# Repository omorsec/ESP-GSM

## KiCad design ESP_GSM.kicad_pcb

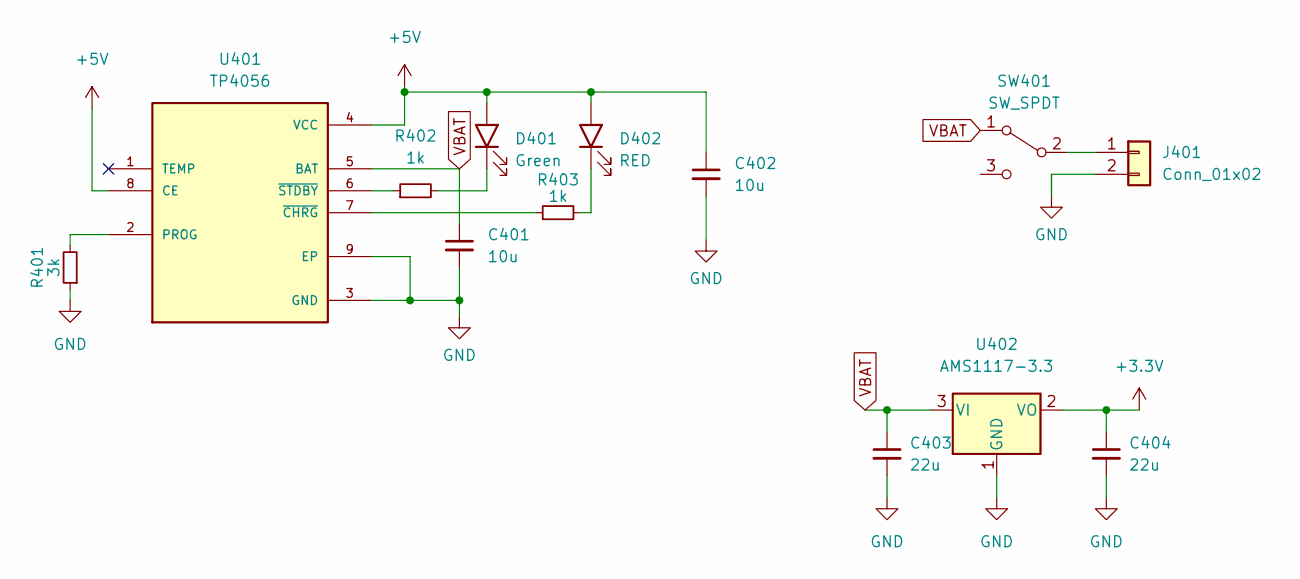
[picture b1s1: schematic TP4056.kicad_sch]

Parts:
C401, C402: 10u; CP_EIA-3216-10_Kemet-I; JLCPCB Part No C7171
C403, C404: 22u; CP_EIA-3216-10_Kemet-I; JLCPCB Part No C782264
D401: Green; LED_0402_1005Metric; JLCPCB Part No C965797
D402: RED; LED_0402_1005Metric; JLCPCB Part No C130719
J401: Conn_01x02; JST_PH_S2B-PH-K_1x02_P2.00mm_Horizontal; JLCPCB Part No C173752
R401: 3k; R_0805_2012Metric; JLCPCB Part No C17661
R402, R403: 1k; R_0402_1005Metric; JLCPCB Part No C2693046
SW401: SW_SPDT; SW_Slide_1P2T_CK_OS102011MS2Q; JLCPCB Part No C393937
U401: TP4056; SOP127P600X175-9N; JLCPCB Part No C16581
U402: AMS1117-3.3; SOT-223-3_TabPin2; JLCPCB Part No C6186

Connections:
+3V3: C404.1, U402.2 (VO); also elsewhere on the board
+5V: C402.1, D401.2 (A), D402.2 (A), U401.4 (VCC), U401.8 (CE); also elsewhere on the board
GND: C401.2, C402.2, C403.2, C404.2, J401.2, R401.1, U401.3 (GND), U401.9 (EP), U402.1 (GND); also elsewhere on the board
unnamed: D401.1 (K), R402.2
unnamed: D402.1 (K), R403.2
unnamed: J401.1, SW401.2 (B)
unnamed: R401.2, U401.2 (PROG)
unnamed: R402.1, U401.6 (~STDBY)
unnamed: R403.1, U401.7 (~CHRG)
VBAT: C401.1, C403.1, SW401.1 (A), U401.5 (BAT), U402.3 (VI); also elsewhere on the board

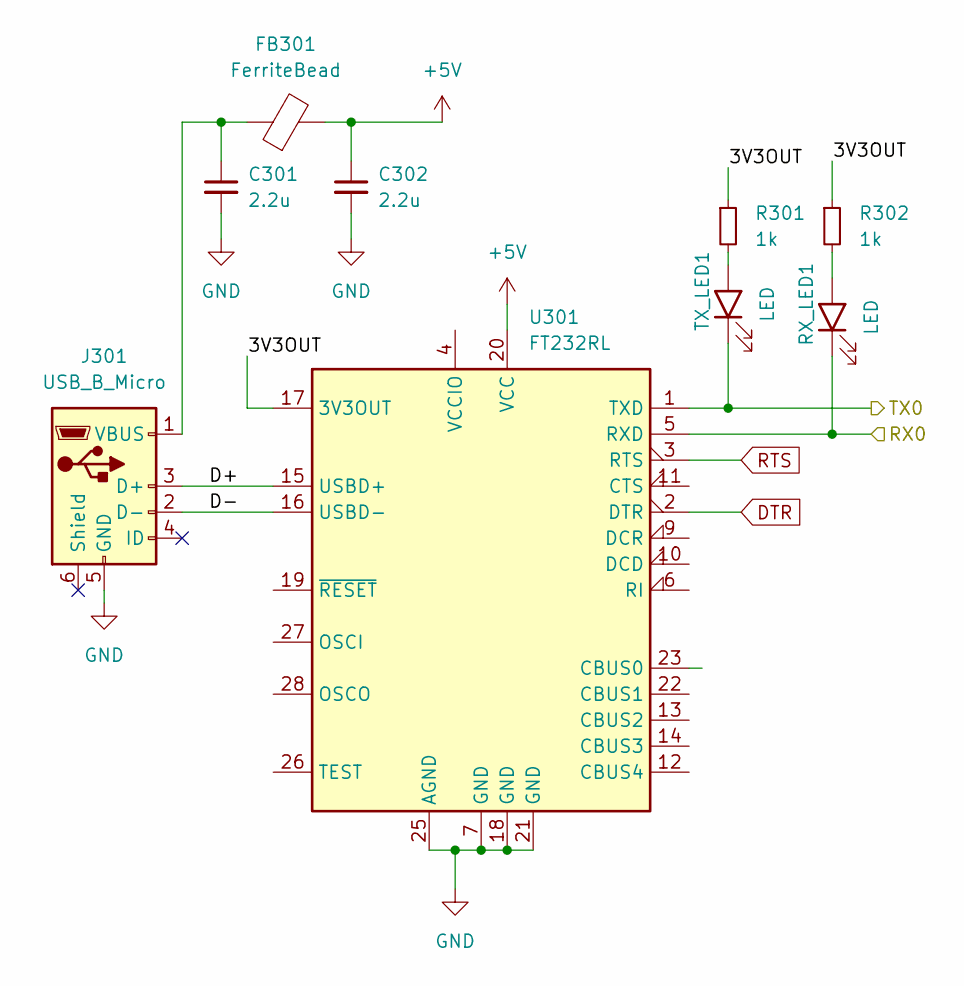
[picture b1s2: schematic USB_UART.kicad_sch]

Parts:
C301, C302: 2.2u; C_0603_1608Metric; JLCPCB Part No C23630
FB301: FerriteBead; L_0805_2012Metric; JLCPCB Part No C1015
J301: USB_B_Micro; USB_Micro-B_Amphenol_10118194_Horizontal; JLCPCB Part No C132563
R301, R302: 1k; R_0402_1005Metric; JLCPCB Part No C2693046
RX_LED1: LED; LED_0402_1005Metric; JLCPCB Part No C130719
TX_LED1: LED; LED_0402_1005Metric; JLCPCB Part No C130719
U301: FT232RL; SSOP-28_5.3x10.2mm_P0.65mm; JLCPCB Part No C8690

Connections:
+5V: C302.1, FB301.2, U301.20 (VCC); also elsewhere on the board
/ESP32/RX0: TX_LED1.1 (K), U301.1 (TXD); also elsewhere on the board
/ESP32/TX0: RX_LED1.1 (K), U301.5 (RXD); also elsewhere on the board
/USB_UART/3V3OUT: R301.1, R302.1, U301.17 (3V3OUT)
/USB_UART/D+: J301.3 (D+), U301.15 (USBD+)
/USB_UART/D-: J301.2 (D-), U301.16 (USBD-)
DTR: U301.2 (DTR); also elsewhere on the board
GND: C301.2, C302.2, J301.5 (GND), U301.7 (GND), U301.18 (GND), U301.21 (GND), U301.25 (AGND); also elsewhere on the board
unnamed: C301.1, FB301.1, J301.1 (VBUS)
unnamed: R301.2, TX_LED1.2 (A)
unnamed: R302.2, RX_LED1.2 (A)
RTS: U301.3 (RTS); also elsewhere on the board

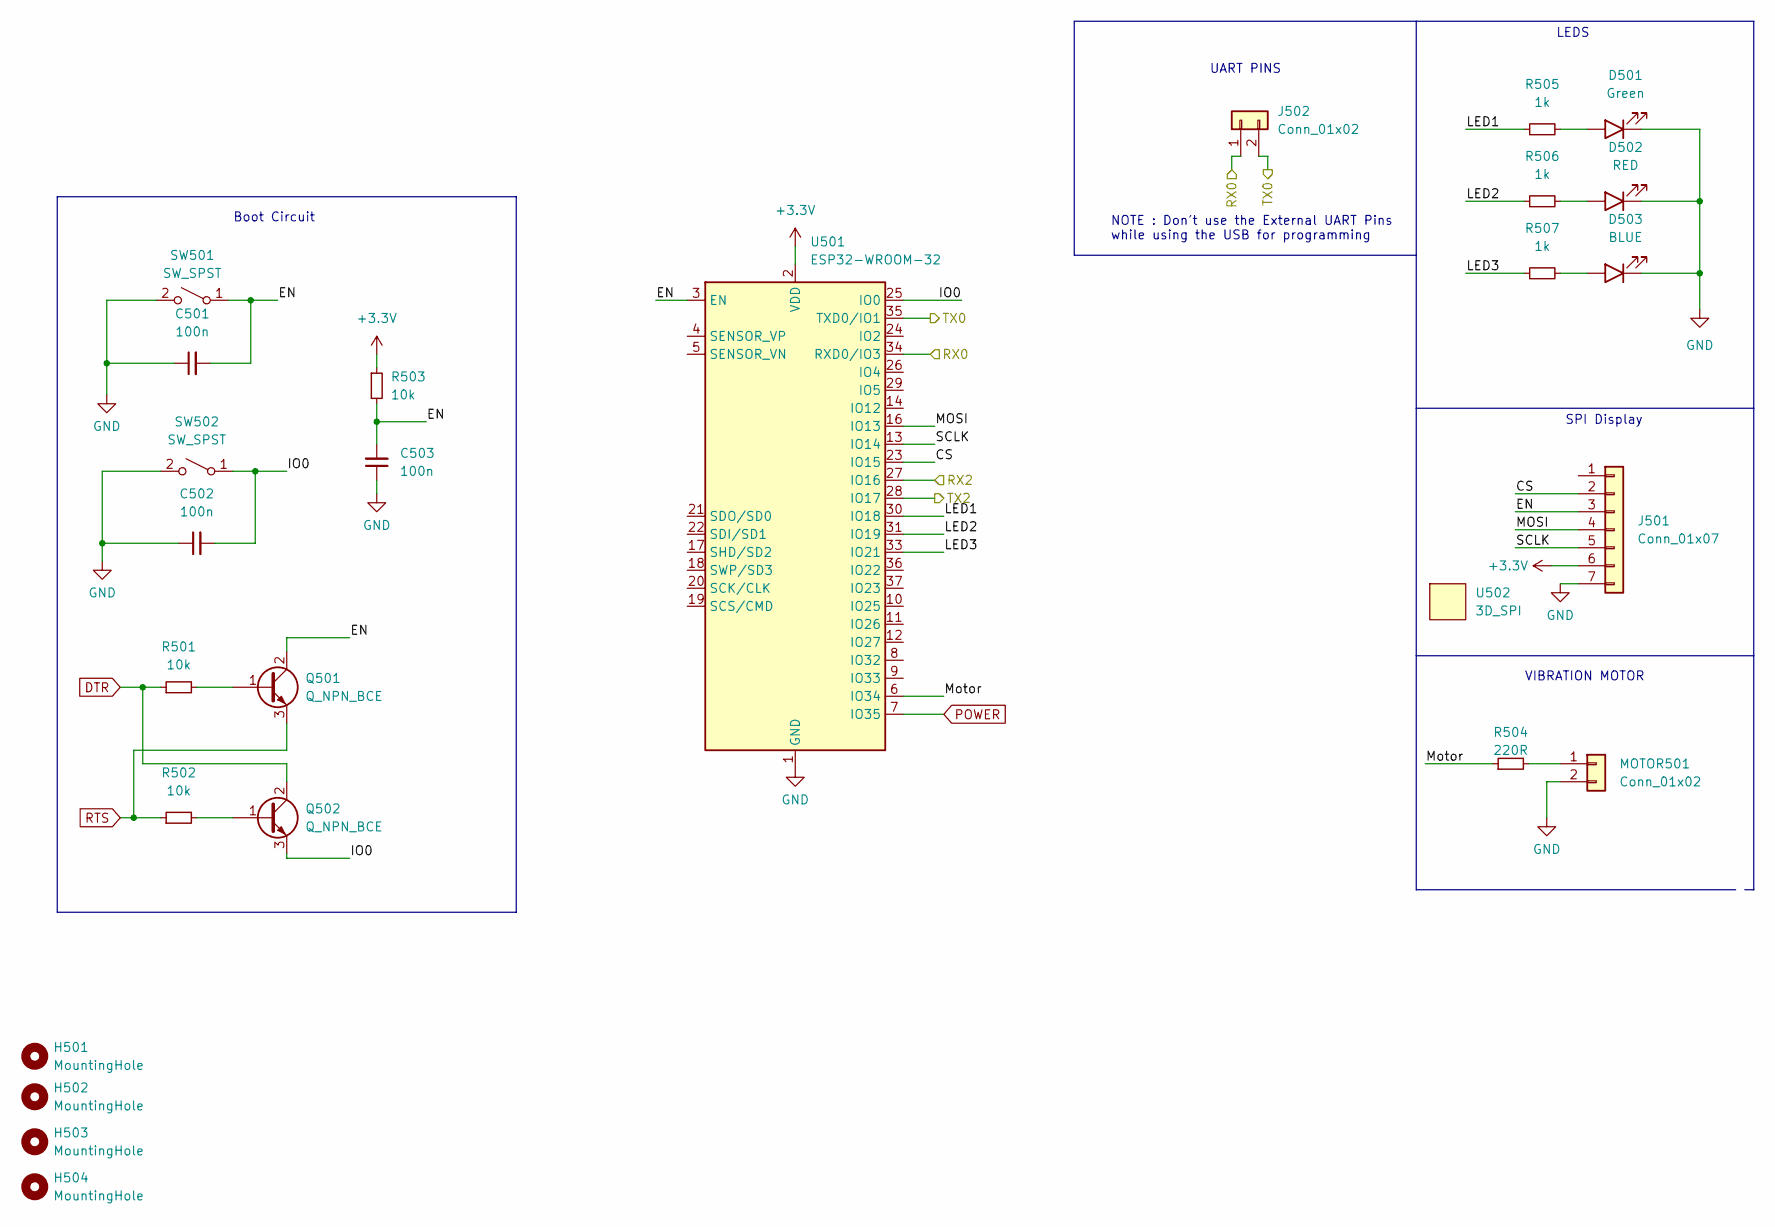
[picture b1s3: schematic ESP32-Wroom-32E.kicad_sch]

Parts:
C501, C502, C503: 100n; C_0402_1005Metric; JLCPCB Part No C1525
D501: Green; LED_0402_1005Metric; JLCPCB Part No C965797
D502: RED; LED_0402_1005Metric; JLCPCB Part No C130719
D503: BLUE; LED_0402_1005Metric; JLCPCB Part No C130724
H501, H502, H503, H504: MountingHole; MountingHole_2mm
J501: Conn_01x07; PinSocket_1x07_P2.54mm_Vertical; JLCPCB Part No C2932672
J502: Conn_01x02; PinSocket_1x02_P2.54mm_Vertical; JLCPCB Part No C49661
MOTOR501: Conn_01x02; TestPoint_2Pads_Pitch2.54mm_Drill0.8mm
Q501, Q502: Q_NPN_BCE; SOT-23; JLCPCB Part No C2150
R501, R502, R503: 10k; R_0805_2012Metric; JLCPCB Part No C17414
R504: 220R; R_0805_2012Metric; JLCPCB Part No C17557
R505, R506, R507: 1k; R_0402_1005Metric; JLCPCB Part No C2693046
SW501, SW502: SW_SPST; SW_SPST_PTS645; JLCPCB Part No C221880
U501: ESP32-WROOM-32; JLCPCB Part No C701341
U502: 3D_SPI; 3D SPI_2

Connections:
+3V3: J501.6, R503.1, U501.2 (VDD); also elsewhere on the board
/ESP32/CS: J501.2, U501.23 (IO15)
/ESP32/EN: C501.2, C503.2, J501.3, Q501.2 (C), R503.2, SW501.1 (A), U501.3 (EN)
/ESP32/IO0: C502.2, Q502.3 (E), SW502.1 (A), U501.25 (IO0)
/ESP32/LED1: R505.1, U501.30 (IO18)
/ESP32/LED2: R506.1, U501.31 (IO19)
/ESP32/LED3: R507.1, U501.33 (IO21)
/ESP32/MOSI: J501.4, U501.16 (IO13)
/ESP32/Motor: R504.1, U501.6 (IO34)
/ESP32/RX0: J502.1, U501.34 (RXD0/IO3); also elsewhere on the board
/ESP32/RX2: U501.27 (IO16); also elsewhere on the board
/ESP32/SCLK: J501.5, U501.13 (IO14)
/ESP32/TX0: J502.2, U501.35 (TXD0/IO1); also elsewhere on the board
/ESP32/TX2: U501.28 (IO17); also elsewhere on the board
DTR: Q502.2 (C), R501.1; also elsewhere on the board
GND: C501.1, C502.1, C503.1, D501.1 (K), D502.1 (K), D503.1 (K), J501.7, MOTOR501.2, SW501.2 (B), SW502.2 (B), U501.1 (GND), U501.15 (GND), U501.38 (GND), U501.39 (GND); also elsewhere on the board
unnamed: D501.2 (A), R505.2
unnamed: D502.2 (A), R506.2
unnamed: D503.2 (A), R507.2
unnamed: MOTOR501.1, R504.2
unnamed: Q501.1 (B), R501.2
unnamed: Q502.1 (B), R502.2
POWER: U501.7 (IO35); also elsewhere on the board
RTS: Q501.3 (E), R502.1; also elsewhere on the board

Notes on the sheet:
LEDS
NOTE : Don't use the External UART Pins while using the USB for programming
Boot Circuit
SPI Display
VIBRATION MOTOR
UART PINS

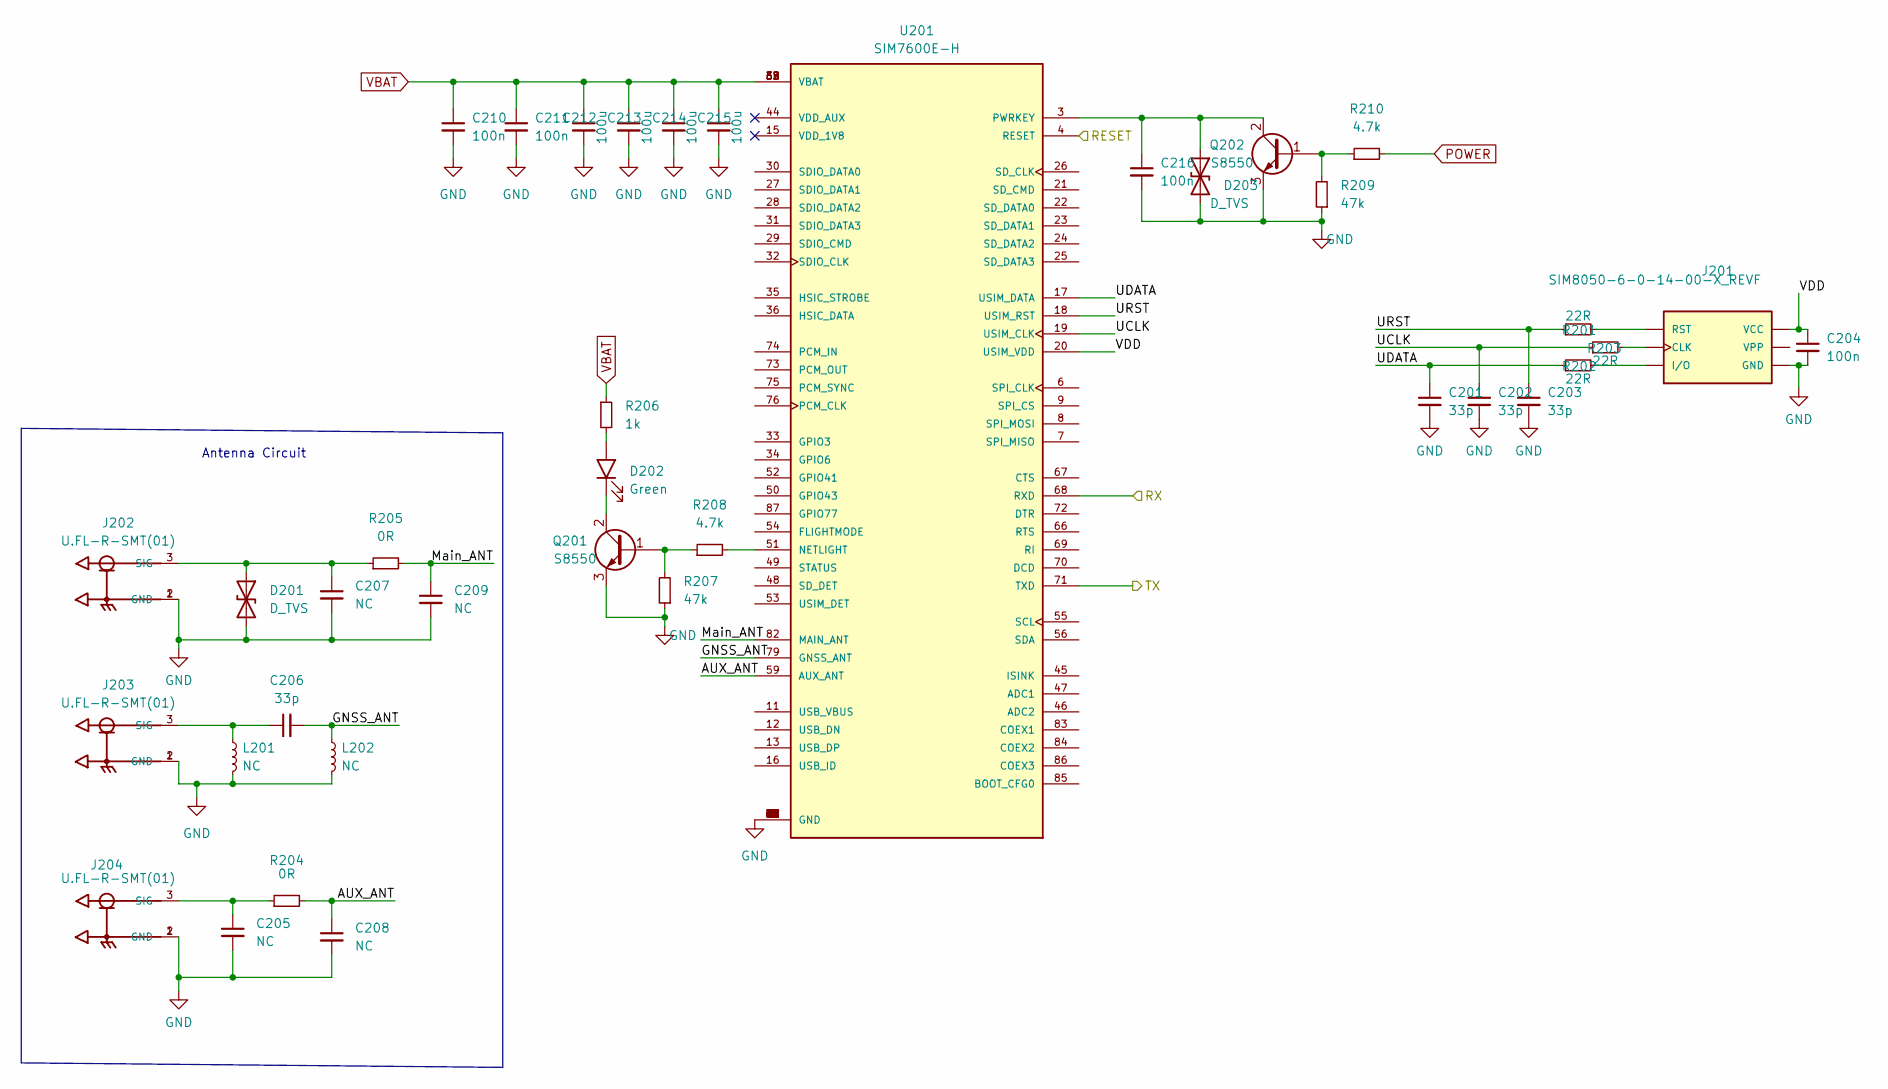
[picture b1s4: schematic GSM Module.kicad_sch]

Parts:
C201, C202, C203, C206: 33p; R_0402_1005Metric; JLCPCB Part No C1562
C204, C210, C211, C216: 100n; C_0402_1005Metric; JLCPCB Part No C1525
C205, C207, C208, C209: NC; C_0805_2012Metric_Pad1.18x1.45mm_HandSolder
C212, C213, C214, C215: 100u; CP_EIA-3528-15_AVX-H; JLCPCB Part No C16133
D201, D203: D_TVS; D_0402_1005Metric; JLCPCB Part No C86141
D202: Green; LED_0402_1005Metric; JLCPCB Part No C965797
J201: SIM8050-6-0-14-00-X_REVF; GCT_SIM8050-6-0-14-00-X_REVF; JLCPCB Part No C266889
J202, J203, J204: U.FL-R-SMT(01); HRS_U.FL-R-SMT(01); JLCPCB Part No C88374
L201, L202: NC; L_0805_2012Metric
Q201, Q202: S8550; SOT-23; JLCPCB Part No C105432
R201, R202, R203: 22R; R_0402_1005Metric; JLCPCB Part No C114765
R204, R205: 0R; R_0402_1005Metric; JLCPCB Part No C17168
R206: 1k; R_0402_1005Metric; JLCPCB Part No C2693046
R207, R209: 47k; R_0402_1005Metric; JLCPCB Part No C144757
R208, R210: 4.7k; R_0402_1005Metric; JLCPCB Part No C25900
U201: SIM7600E-H; IC_SIM7600E-H; PARTREV 1.01; JLCPCB Part No C520536

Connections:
/ESP32/RX2: U201.71 (TXD); also elsewhere on the board
/ESP32/TX2: U201.68 (RXD); also elsewhere on the board
/GSM_USB/AUX_ANT: C208.1, R204.2, U201.59 (AUX_ANT)
/GSM_USB/GNSS_ANT: C206.2, L202.1, U201.79 (GNSS_ANT)
/GSM_USB/Main_ANT: C209.1, R205.2, U201.82 (MAIN_ANT)
/GSM_USB/RESET: U201.4 (RESET)
/GSM_USB/UCLK: C202.1, R203.1, U201.19 (USIM_CLK)
/GSM_USB/UDATA: C201.1, R202.1, U201.17 (USIM_DATA)
/GSM_USB/URST: C203.1, R201.1, U201.18 (USIM_RST)
/GSM_USB/VDD: C204.1, J201.C1 (VCC), U201.20 (USIM_VDD)
GND: C201.2, C202.2, C203.2, C204.2, C205.2, C207.2, C208.2, C209.2, C210.2, C211.2, C212.2, C213.2, C214.2, C215.2, C216.2, D201.2 (A2), D203.2 (A2), J201.C4 (GND), J201.C5 (GND), J201.C8 (GND), J202.1 (GND), J202.2 (GND), J203.1 (GND), J203.2 (GND), J204.1 (GND), J204.2 (GND), L201.2, L202.2, Q201.3 (E), Q202.3 (E), R207.1, R209.1, U201.1 (GND), U201.2 (GND), U201.5 (GND), U201.10 (GND), U201.14 (GND), U201.37 (GND), U201.40 (GND), U201.41 (GND), U201.43 (GND), U201.57 (GND), U201.58 (GND), U201.60 (GND), U201.61 (GND), U201.64 (GND), U201.65 (GND), U201.77 (GND), U201.78 (GND), U201.80 (GND), U201.81 (GND); also elsewhere on the board
unnamed: C205.1, J204.3 (SIG), R204.1
unnamed: C206.1, J203.3 (SIG), L201.1
unnamed: C207.1, D201.1 (A1), J202.3 (SIG), R205.1
unnamed: C216.1, D203.1 (A1), Q202.2 (C), U201.3 (PWRKEY)
unnamed: D202.1 (K), Q201.2 (C)
unnamed: D202.2 (A), R206.2
unnamed: J201.C2 (RST), R201.2
unnamed: J201.C3 (CLK), R203.2
unnamed: J201.C7 (I/O), R202.2
unnamed: Q201.1 (B), R207.2, R208.1
unnamed: Q202.1 (B), R209.2, R210.1
unnamed: R208.2, U201.51 (NETLIGHT)
POWER: R210.2; also elsewhere on the board
VBAT: C210.1, C211.1, C212.1, C213.1, C214.1, C215.1, R206.1, U201.38 (VBAT), U201.39 (VBAT), U201.62 (VBAT), U201.63 (VBAT); also elsewhere on the board

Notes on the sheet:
Antenna Circuit

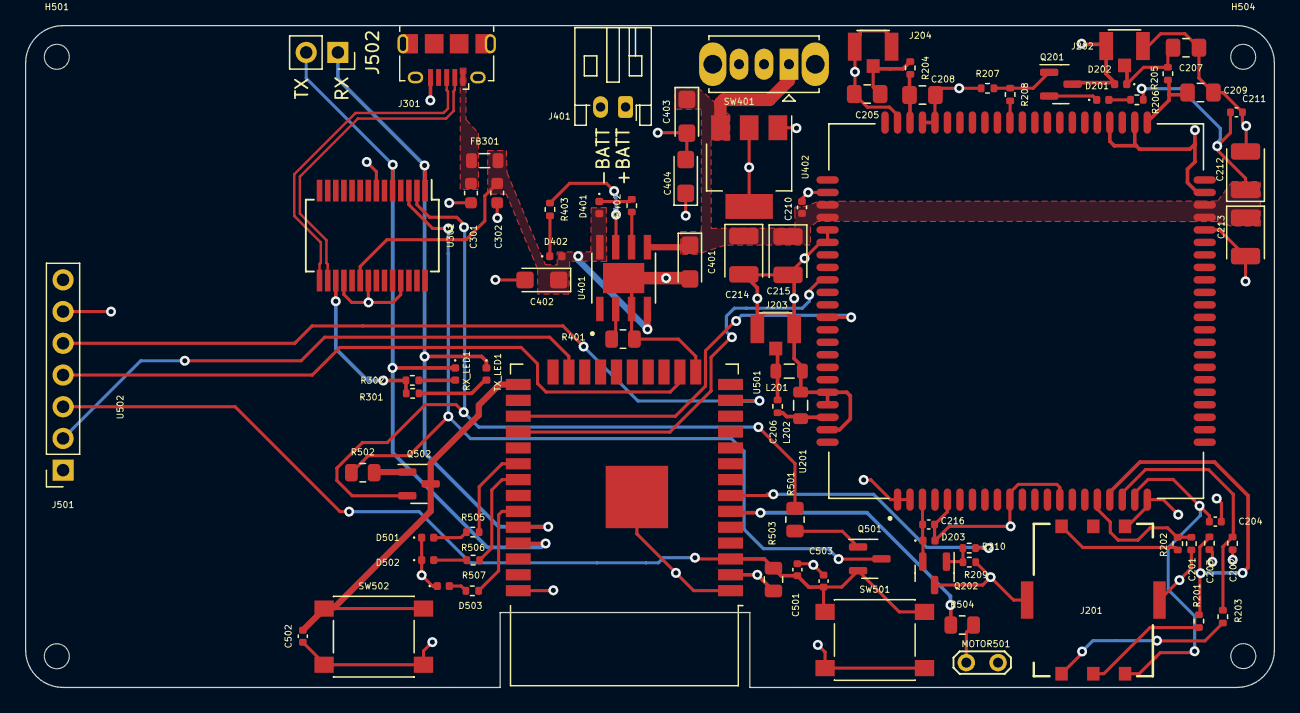
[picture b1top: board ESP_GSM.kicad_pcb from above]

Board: 4 copper layers, 100.0 x 53.0 mm, 86 parts (0 on the bottom side), 57 nets.

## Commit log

2023-01-13 Latest Update to all files
